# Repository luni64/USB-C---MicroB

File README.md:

See also https://forum.pjrc.com/threads/65654-USB-C-Adapter

# USB-C_Adapter
Breadboard friendly USB-C to USB-MicroB adapter

BOM: https://octopart.com/bom-tool/3KlzNDGG

Solder pin header AFTER plugging the adapter & board in a breadboard. Aligning distances to account for tolerances before soldering pin header.

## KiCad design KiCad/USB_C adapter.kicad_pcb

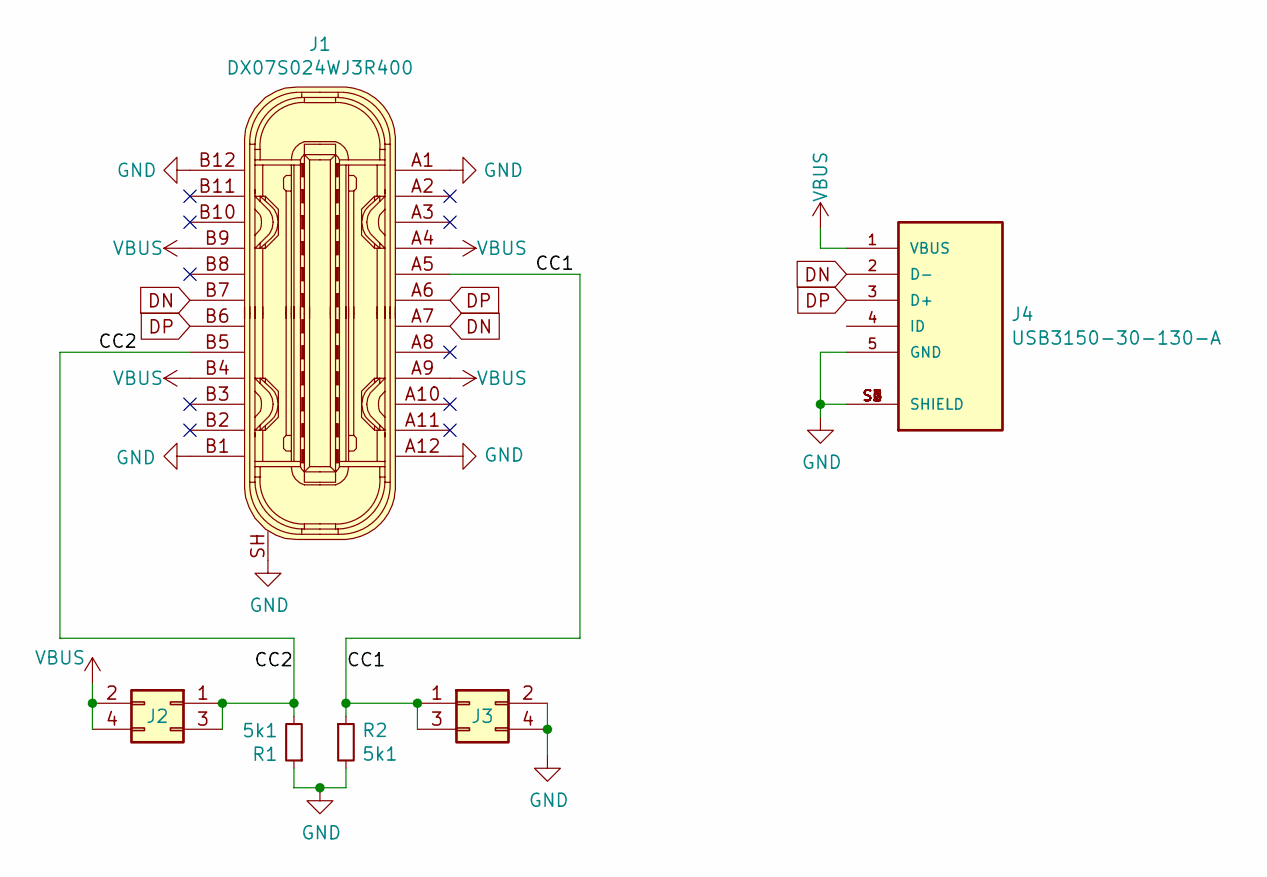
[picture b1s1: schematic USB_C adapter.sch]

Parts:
J1: DX07S024WJ3R400; USB-C_Female_Vert_DX07S024WJ3R400; MPN DX07S024WJ3R400; Digi-Key_PN 670-2950-1-ND
J2, J3: Conn_02x02_Odd_Even; PinHeader_2x02_P2.54mm_Horizontal
J4: USB3150-30-130-A; GCT_USB3150-30-130-A; PARTREV A2
R1, R2: 5k1; R_0805_2012Metric_Pad1.15x1.40mm_HandSolder

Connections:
/CC1: J1.A5, J3.1, J3.3, R2.1
/CC2: J1.B5, J2.1, J2.3, R1.2
DN: J1.A7, J1.B7, J4.2 (D-)
DP: J1.A6, J1.B6, J4.3 (D+)
GND: J1.A1, J1.A12, J1.B1, J1.B12, J1.SH, J3.2, J3.4, J4.5 (GND), J4.S1 (SHIELD), J4.S2 (SHIELD), J4.S3 (SHIELD), J4.S4 (SHIELD), J4.S5 (SHIELD), J4.S6 (SHIELD), R1.1, R2.2
VBUS: J1.A4, J1.A9, J1.B4, J1.B9, J2.2, J2.4, J4.1 (VBUS)

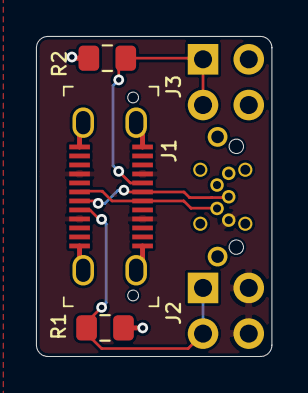
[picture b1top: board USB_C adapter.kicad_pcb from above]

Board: 2 copper layers, 13.1 x 17.8 mm, 6 parts (1 on the bottom side), 6 nets.

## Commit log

2021-01-16 images
2021-01-16 filenames
